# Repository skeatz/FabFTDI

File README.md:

# FabFTDI Projects
This repository contains all my FabFTDI projects:
FabFTDI projects which make use of avr microcontrollers are based on the V-USB library from [obdev](https://www.obdev.at/products/vusb/index.html) and the AVR-CDC work done by [K Ishikawa](http://www.recursion.jp/prose/avrcdc/) at recursion.jp.

A few points about the AVR-CDC protocol with Atmel microcontrollers - AVR-CDC enables a PC to communicate with a low-speed USB device (AVR microcontroller) through a virtual COM port.

The table below (from **recursion.jp**) lists the specifications for AVR-CDC with different AVR microcontrollers:
* AVR-CDC with USART (ATmega8/48/88/168/328)
    * speed: 600 - 38400 bps
    * datasize: 5 - 8 bits
    * parity: none/even/odd
    * stopbit: 1/2
    * controls: DTR, RTS, CTS
* AVR-CDC with USART (ATtiny2313)
    * speed: 600 - 38400 bps
    * datasize: 8
    * parity: none
    * stopbit: 1
* AVR-CDC without USART (ATtiny45/85)
    * speed: 1200 - 4800 bps
    * datasize: 8
    * stopbit: 1...

1. **[CH340G-based FabFTDI](fabftdi-ch340g.md)**
   * speeds up to 2 Mbps (loopback)
   * tested up to 250 kbps with ESP8266 module
   * uses hardware USB-to-TTL chip
   * low cost (USD0.40 per IC for 10 pcs)
2. **[ATmega8-based FabFTDI](fabftdi-mega8.md)**
   * speeds up to 2 Mbps (loopback)
   * tested up to 250 kbps with ESP8266 module
   * hardware UART
   * uses V-USB/AVR-CDC library
3. **[ATtiny2313-based FabFTDI](fabftdi-tiny2313.md)**
   * speed up to 57600 bps
   * hardware UART
   * uses V-USB library
4. **[ATtiny45-based FabFTDI (w/crystal)](fabftdi-tiny45x.md)**
   * speeds up to 4800 bps
   * uses V-USB library
5. **[ATtiny45-based FabFTDI (w/internal PLL)](fabftdi-tiny45.md)**
   * speeds up to 4800 bps
   * uses V-USB library

Collection of FabFTDI boards (from left): CH340g-based, ATmega8-based, ATtiny2313-based, ATtiny45-based w/crystal, ATtiny45-based w/internal oscillator

*Copyright (c) Steven Chew*...

*MIT license*

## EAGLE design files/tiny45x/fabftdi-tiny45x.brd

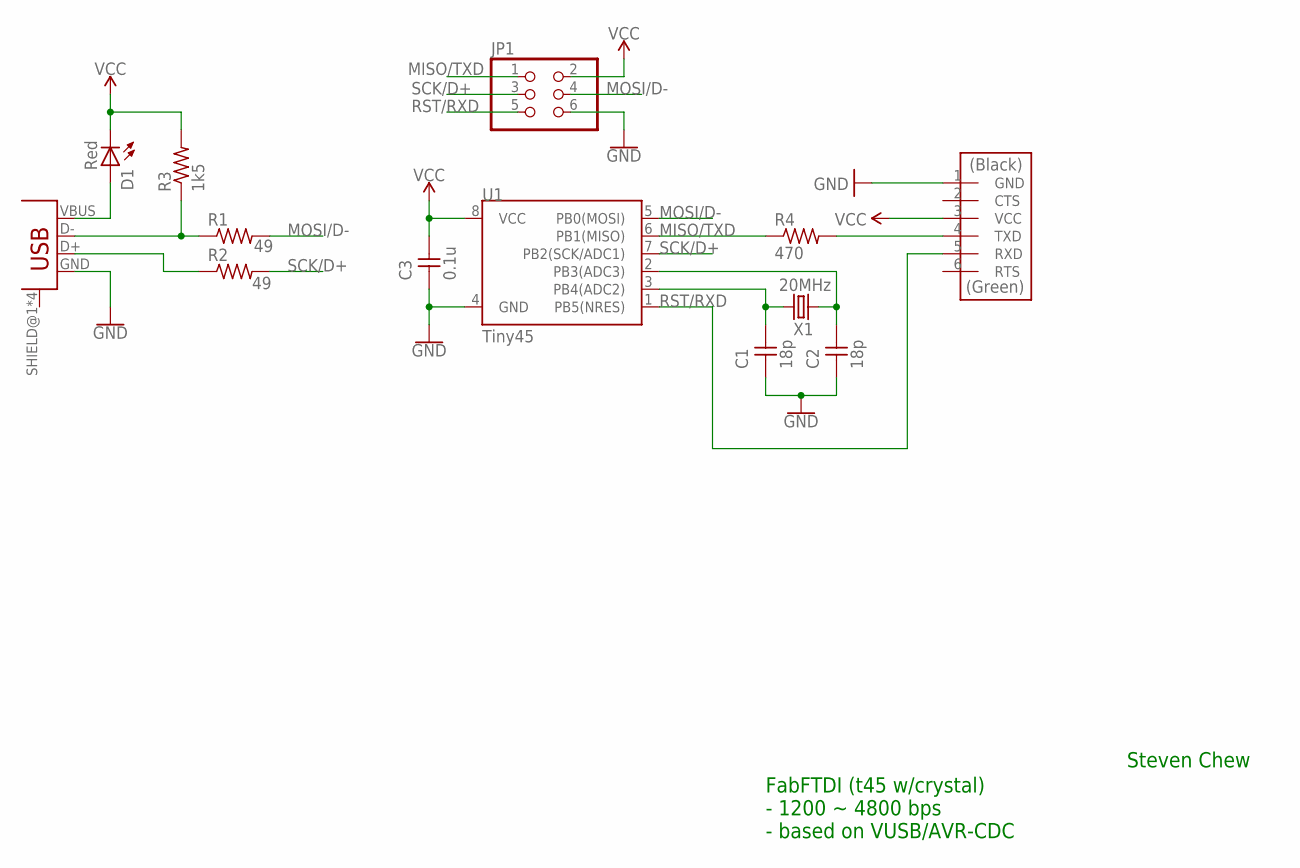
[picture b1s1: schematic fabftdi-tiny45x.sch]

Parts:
C1, C2: 18p; C1206FAB
C3: 0.1u; C1206FAB
D1: Red; LED1206FAB
JP1: PINHD-2X3-SMDFAB; 2X03SMD-FAB
JP2: FTDI-SMD-HEADER; 1X06SMD
R1, R2: 49; R1206FAB
R3: 1k5; R1206FAB
R4: 470; R1206FAB
U1: Tiny45; SO08-EIAJ
U2: USB_MINI
X1: 20MHz; 2-SMD-5X3MM

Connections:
GND: C1.1, C2.1, C3.1, JP1.6, JP2.1 (GND), U1.4 (GND), U2.GND
MISO/TXD: JP1.1, R4.1, U1.6 (PB1(MISO))
MOSI/D-: JP1.4, R1.2, U1.5 (PB0(MOSI))
unnamed: R1.1, R3.1, U2.D-
unnamed: R2.1, U2.D+
unnamed: D1.1 (A), U2.VBUS
unnamed: C1.2, U1.3 (PB4(ADC2)), X1.P$2 (2)
unnamed: C2.2, U1.2 (PB3(ADC3)), X1.P$1 (1)
unnamed: JP2.4 (TXD), R4.2
RST/RXD: JP1.5, JP2.5 (RXD), U1.1 (PB5(NRES))
SCK/D+: JP1.3, R2.2, U1.7 (PB2(SCK/ADC1))
VCC: C3.2, D1.2 (C), JP1.2, JP2.3 (VCC), R3.2, U1.8 (VCC)

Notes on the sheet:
Steven Chew
FabFTDI (t45 w/crystal) - 1200 ~ 4800 bps - based on VUSB/AVR-CDC

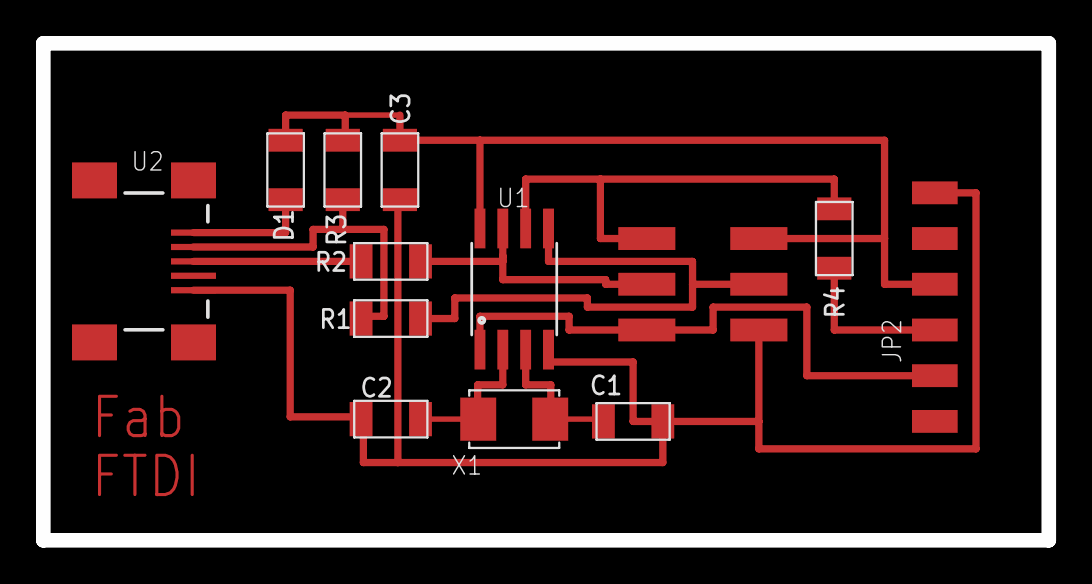
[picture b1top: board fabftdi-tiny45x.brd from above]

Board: 2 copper layers, 55.9 x 27.6 mm, 13 parts (0 on the bottom side), 12 nets.

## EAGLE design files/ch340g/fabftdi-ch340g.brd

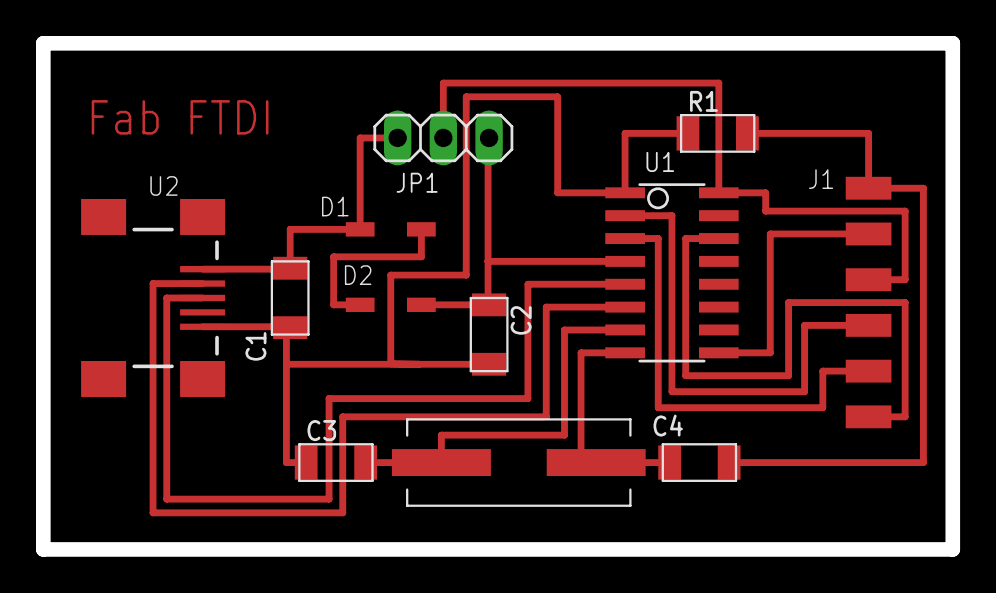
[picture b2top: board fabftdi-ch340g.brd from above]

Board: 2 copper layers, 50.5 x 28.1 mm, 12 parts (0 on the bottom side), 14 nets.

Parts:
C1: 10u; C1206FAB
C2: 10n; C1206FAB
C3, C4: 22p; C1206FAB
D1, D2: SOD123
J1: FTDI; 1X06SMD
JP1: 1X03
R1: 0; R1206FAB
U1: CH340G; SOIC16
U2: USB_MINIB
Y1: 12MHz; CRYSTAL-SMD-10.5X4.8-2PIN

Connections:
3V3: C2.1, D2.CATHODE, JP1.3, U1.4
5V: C1.1, D1.ANODE, JP1.1, U2.VBUS
D+: U1.5, U2.D+
D-: U1.6, U2.D-
GND: C1.2, C2.2, C3.1, R1.1, U1.1, U2.GND
GND': C4.1, J1.1, R1.2
unnamed: C4.2, U1.8, Y1.P$1
unnamed: C3.2, U1.7, Y1.P$2
unnamed: D1.CATHODE, D2.ANODE
unnamed: J1.2, U1.9
unnamed: J1.4, U1.2
unnamed: J1.5, U1.3
unnamed: J1.6, U1.14
VCC: J1.3, JP1.2, U1.16

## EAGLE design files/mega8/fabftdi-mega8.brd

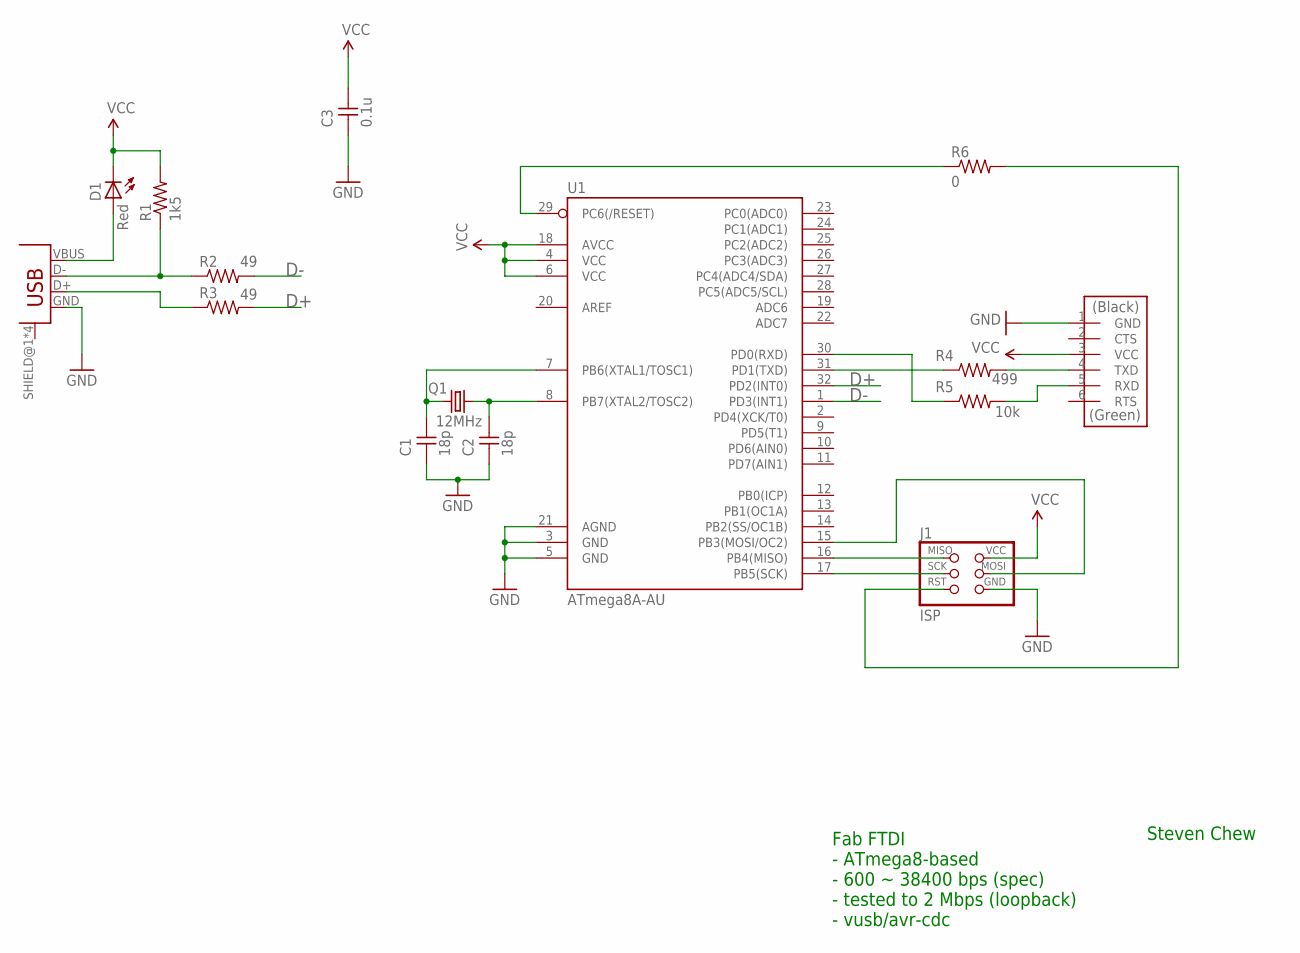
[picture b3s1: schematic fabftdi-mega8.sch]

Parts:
C1, C2: 18p; C1206FAB
C3: 0.1u; C1206FAB
D1: Red; LED1206FAB
J1: ISP; 2X03SMD
J2: FTDI-SMD-HEADER; 1X06SMD
Q1: 12MHz; HC49UP
R1: 1k5; R1206FAB
R2, R3: 49; R1206FAB
R4: 499; R1206FAB
R5: 10k; R1206FAB
R6: 0; R1206FAB
U1: ATmega8A-AU; TQFP32-08THIN
U2: USB_MINI

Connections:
D+: R3.2, U1.32 (PD2(INT0))
D-: R2.2, U1.1 (PD3(INT1))
GND: C1.1, C2.1, C3.1, J1.6 (GND), J2.1 (GND), U1.3 (GND), U1.5 (GND), U1.21 (AGND), U2.GND
unnamed: C2.2, Q1.2, U1.8 (PB7(XTAL2/TOSC2))
unnamed: C1.2, Q1.1, U1.7 (PB6(XTAL1/TOSC1))
unnamed: R4.1, U1.31 (PD1(TXD))
unnamed: R5.1, U1.30 (PD0(RXD))
unnamed: J1.1 (MISO), U1.16 (PB4(MISO))
unnamed: D1.1 (A), U2.VBUS
unnamed: R1.1, R2.1, U2.D-
unnamed: R3.1, U2.D+
unnamed: J1.3 (SCK), U1.17 (PB5(SCK))
unnamed: J1.4 (MOSI), U1.15 (PB3(MOSI/OC2))
unnamed: J2.4 (TXD), R4.2
unnamed: J1.5 (RST), R6.2
unnamed: R6.1, U1.29 (PC6(/RESET))
unnamed: J2.5 (RXD), R5.2
VCC: C3.2, D1.2 (C), J1.2 (VCC), J2.3 (VCC), R1.2, U1.4 (VCC), U1.6 (VCC), U1.18 (AVCC)

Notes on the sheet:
Steven Chew
Fab FTDI - ATmega8-based - 600 ~ 38400 bps (spec) - tested to 2 Mbps (loopback) - vusb/avr-cdc

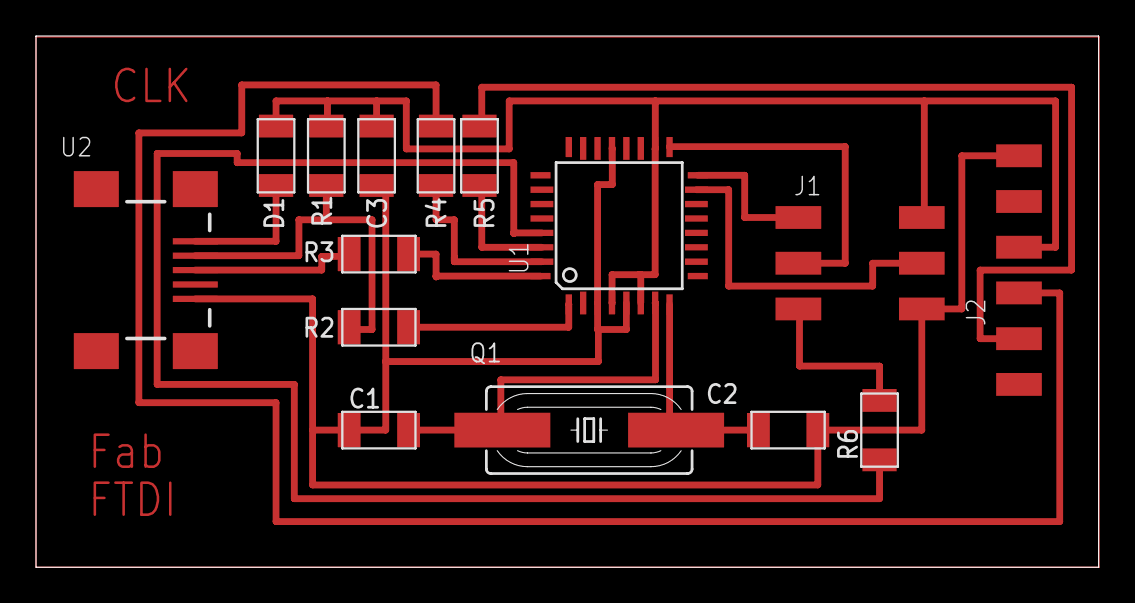
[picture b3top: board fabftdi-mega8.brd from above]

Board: 2 copper layers, 59.0 x 29.5 mm, 15 parts (0 on the bottom side), 18 nets.

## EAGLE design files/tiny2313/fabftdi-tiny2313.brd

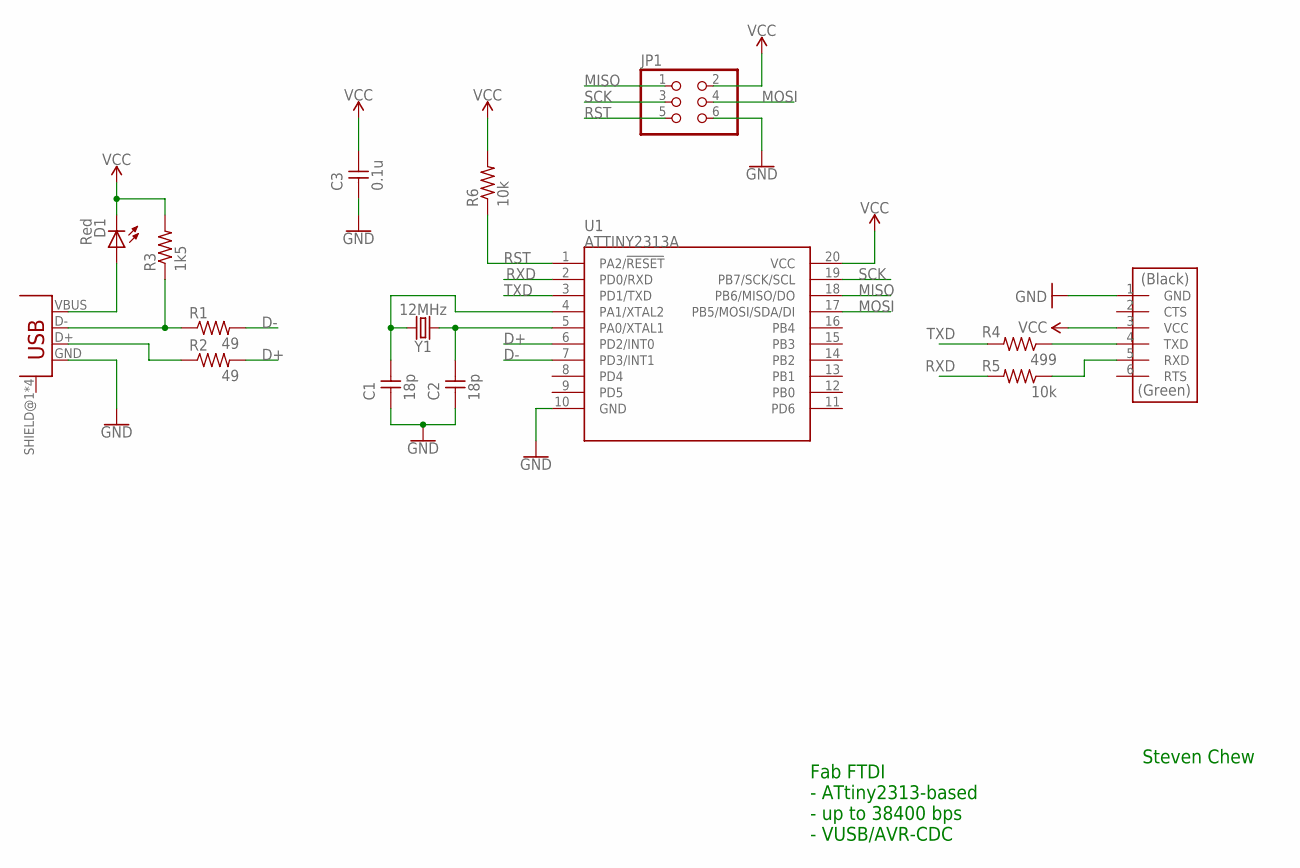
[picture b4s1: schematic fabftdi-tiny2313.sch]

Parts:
C1, C2: 18p; C1206FAB
C3: 0.1u; C1206FAB
D1: Red; LED1206FAB
JP1: PINHD-2X3-SMDFAB; 2X03SMD-FAB
JP2: FTDI-SMD-HEADER; 1X06SMD
R1, R2: 49; R1206FAB
R3: 1k5; R1206FAB
R4: 499; R1206FAB
R5, R6: 10k; R1206FAB
U1: ATTINY2313A; SOP20W
U2: USB_MINI
Y1: 12MHz; HC49UP

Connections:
D+: R2.2, U1.6 (PD2/INT0)
D-: R1.2, U1.7 (PD3/INT1)
GND: C1.1, C2.1, C3.1, JP1.6, JP2.1 (GND), U1.10 (GND), U2.GND
MISO: JP1.1, U1.18 (PB6/MISO/DO)
MOSI: JP1.4, U1.17 (PB5/MOSI/SDA/DI)
unnamed: D1.1 (A), U2.VBUS
unnamed: C2.2, U1.5 (PA0/XTAL1), Y1.1
unnamed: C1.2, U1.4 (PA1/XTAL2), Y1.2
unnamed: JP2.4 (TXD), R4.1
unnamed: JP2.5 (RXD), R5.1
unnamed: R1.1, R3.1, U2.D-
unnamed: R2.1, U2.D+
RST: JP1.5, R6.1, U1.1 (PA2/!RESET)
RXD: R5.2, U1.2 (PD0/RXD)
SCK: JP1.3, U1.19 (PB7/SCK/SCL)
TXD: R4.2, U1.3 (PD1/TXD)
VCC: C3.2, D1.2 (C), JP1.2, JP2.3 (VCC), R3.2, R6.2, U1.20 (VCC)

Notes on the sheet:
Steven Chew
Fab FTDI - ATtiny2313-based - up to 38400 bps - VUSB/AVR-CDC

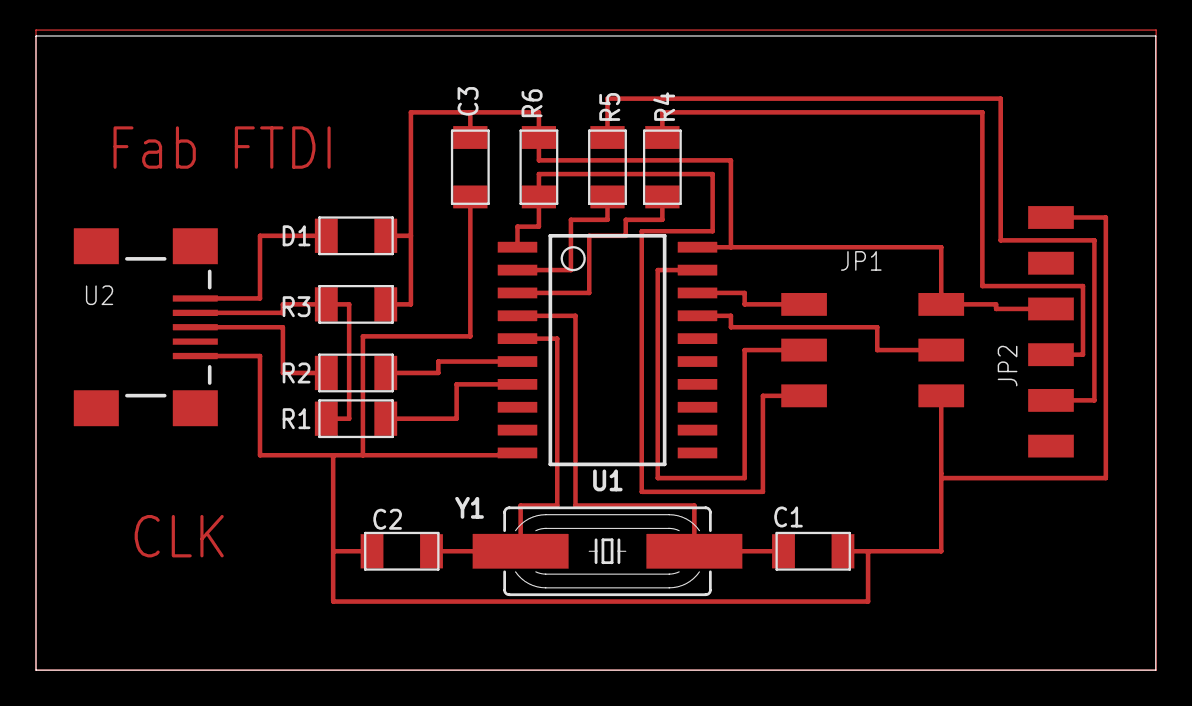
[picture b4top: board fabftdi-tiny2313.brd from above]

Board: 2 copper layers, 62.2 x 35.2 mm, 15 parts (0 on the bottom side), 17 nets.

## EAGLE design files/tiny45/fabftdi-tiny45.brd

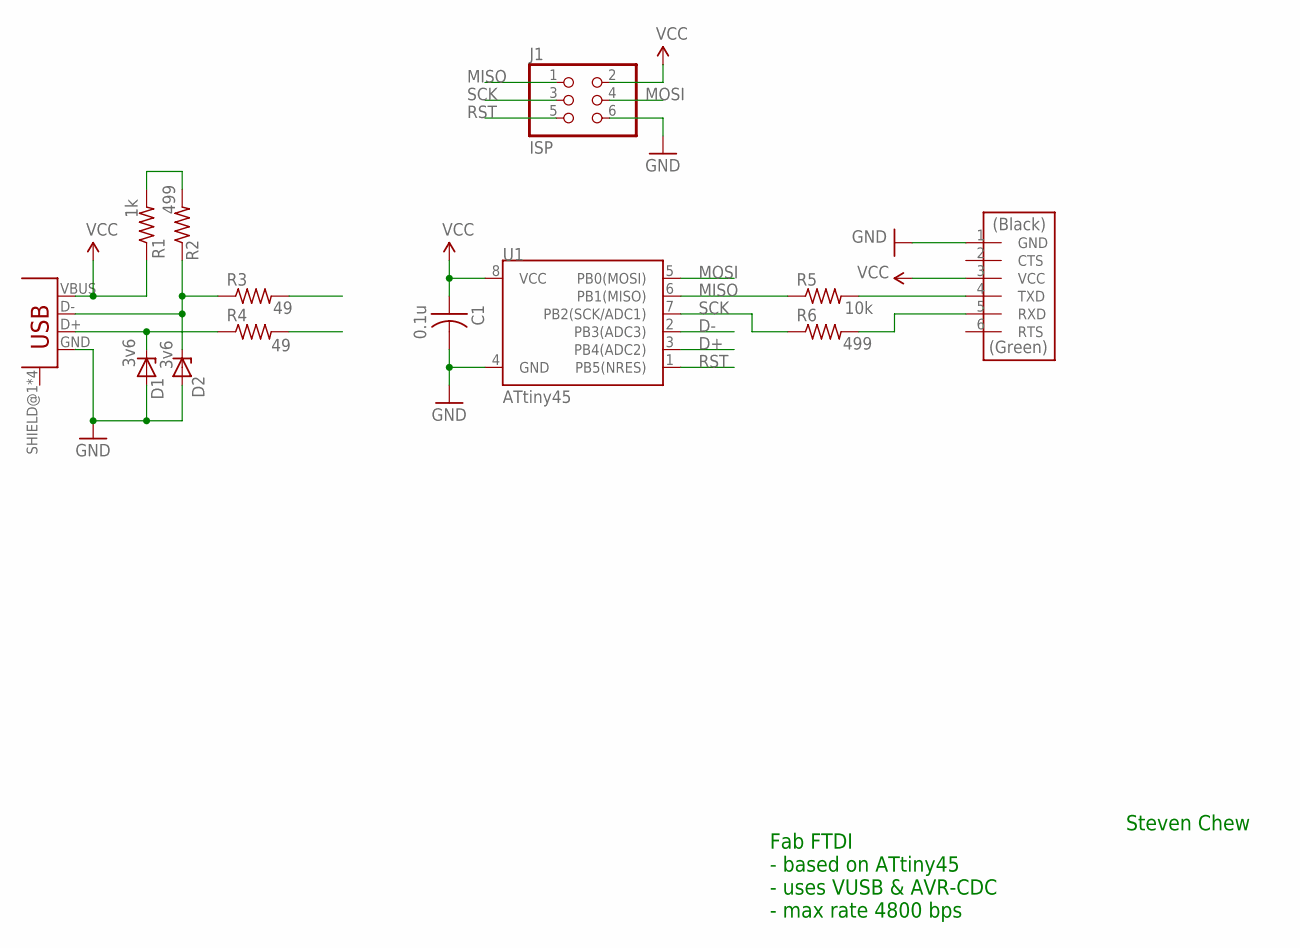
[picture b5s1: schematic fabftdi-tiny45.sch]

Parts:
C1: 0.1u; C1206FAB
D1, D2: 3v6; SOD123
J1: ISP; 2X03SMD-FAB
J2: FTDI-SMD-HEADER; 1X06SMD
R1: 1k; R1206FAB
R2, R6: 499; R1206FAB
R3, R4: 49; R1206FAB
R5: 10k; R1206FAB
U1: ATtiny45; SO08-EIAJ
U2: USB_MINI

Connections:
D+: R4.2, U1.3 (PB4(ADC2))
D-: R3.2, U1.2 (PB3(ADC3))
GND: C1.2, D1.ANODE, D2.ANODE, J1.6, J2.1 (GND), U1.4 (GND), U2.GND
MISO: J1.1, R5.1, U1.6 (PB1(MISO))
MOSI: J1.4, U1.5 (PB0(MOSI))
unnamed: D1.CATHODE, R4.1, U2.D+
unnamed: D2.CATHODE, R2.1, R3.1, U2.D-
unnamed: R1.2, R2.2
unnamed: J2.4 (TXD), R5.2
unnamed: J2.5 (RXD), R6.2
RST: J1.5, U1.1 (PB5(NRES))
SCK: J1.3, R6.1, U1.7 (PB2(SCK/ADC1))
VCC: C1.1, J1.2, J2.3 (VCC), R1.1, U1.8 (VCC), U2.VBUS

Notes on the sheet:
Steven Chew
Fab FTDI - based on ATtiny45 - uses VUSB & AVR-CDC - max rate 4800 bps

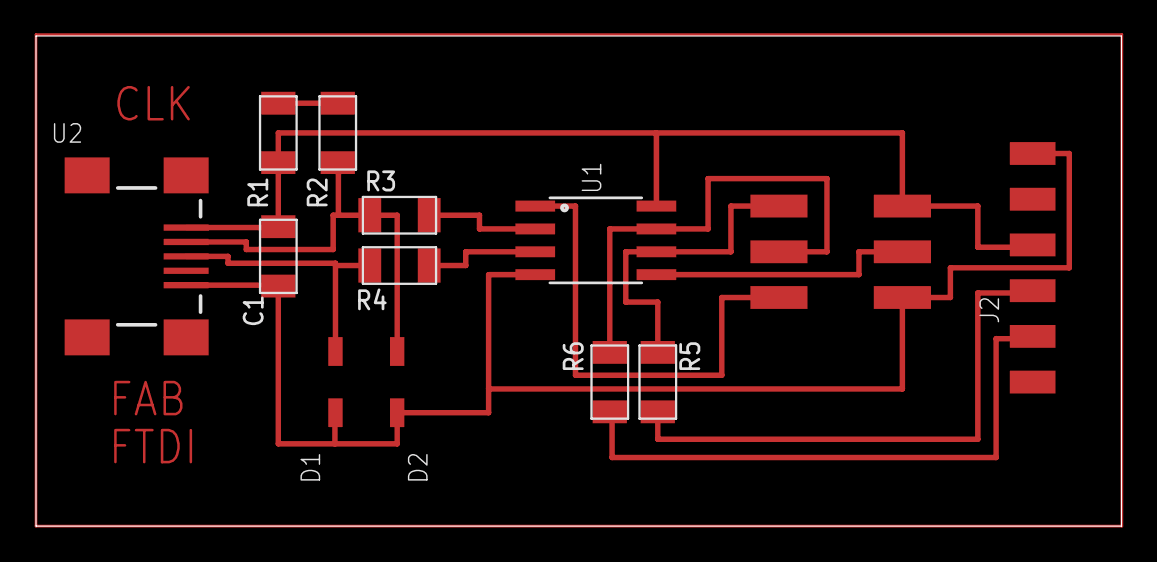
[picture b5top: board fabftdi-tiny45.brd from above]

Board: 2 copper layers, 60.3 x 27.2 mm, 13 parts (0 on the bottom side), 13 nets.

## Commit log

2017-07-04 Added CH340g FTDI
2017-07-04 fixed error in ch340g.md
2017-07-04 fixed ch340g files link
2017-07-04 fixed project highlights in readme.md
2017-07-04 added link to ch340g project
2017-07-04 added design files for other FabFTDI
2017-07-04 added tutorial for mega8
2017-07-04 fixed error in mega8 writeup
2017-07-04 fixed headers in mega8.md
2017-07-05 updated readme & mega8
2017-07-15 Added fabmodules board outline & traces
2017-07-15 updated mega8 eagle files
2017-07-15 added t2313 fabftdi
2017-07-15 updated filename tiny2313
2017-07-15 updated t2313 links
2017-07-15 Fixed avrdude error
2017-07-15 added board collection
2017-07-16 updated all files, added components list
2017-07-16 Updated mega8 files
2017-07-16 updated md files

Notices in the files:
parts and their libraries:
SparkFun-FreqCtrl: Licensing: Creative Commons ShareAlike 4.0 International - https://creativecommons.org/licenses/by-sa/4.0
